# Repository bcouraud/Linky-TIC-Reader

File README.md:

# dongle_Linky

## Getting started

To make it easy for you to get started with GitLab, here's a list of recommended next steps.

Already a pro? Just edit this README.md and make it your own. Want to make it easy? [Use the template at the bottom](#editing-this-readme)!

## Add your files

- [ ] [Create](https://docs.gitlab.com/ee/user/project/repository/web_editor.html#create-a-file) or [upload](https://docs.gitlab.com/ee/user/project/repository/web_editor.html#upload-a-file) files
- [ ] [Add files using the command line](https://docs.gitlab.com/ee/gitlab-basics/add-file.html#add-a-file-using-the-command-line) or push an existing Git repository with the following command:

```
cd existing_repo
git remote add origin https://tip-imredd.unice.fr/code/energy/dongle_linky.git
git branch -M master
git push -uf origin master
```

## Integrate with your tools

- [ ] [Set up project integrations](https://tip-imredd.unice.fr/code/energy/dongle_linky/-/settings/integrations)

## Collaborate with your team

- [ ] [Invite team members and collaborators](https://docs.gitlab.com/ee/user/project/members/)
- [ ] [Create a new merge request](https://docs.gitlab.com/ee/user/project/merge_requests/creating_merge_requests.html)
- [ ] [Automatically close issues from merge requests](https://docs.gitlab.com/ee/user/project/issues/managing_issues.html#closing-issues-automatically)
- [ ] [Enable merge request approvals](https://docs.gitlab.com/ee/user/project/merge_requests/approvals/)
- [ ] [Set auto-merge](https://docs.gitlab.com/ee/user/project/merge_requests/merge_when_pipeline_succeeds.html)

## Test and Deploy

Use the built-in continuous integration in GitLab.

- [ ] [Get started with GitLab CI/CD](https://docs.gitlab.com/ee/ci/quick_start/index.html)
- [ ] [Analyze your code for known vulnerabilities with Static Application Security Testing (SAST)](https://docs.gitlab.com/ee/user/application_security/sast/)
- [ ] [Deploy to Kubernetes, Amazon EC2, or Amazon ECS using Auto Deploy](https://docs.gitlab.com/ee/topics/autodevops/requirements.html)
- [ ] [Use pull-based deployments for improved Kubernetes management](https://docs.gitlab.com/ee/user/clusters/agent/)
- [ ] [Set up protected environments](https://docs.gitlab.com/ee/ci/environments/protected_environments.html)

***

# Editing this README

When you're ready to make this README your own, just edit this file and use the handy template below (or feel free to structure it however you want - this is just a starting point!). Thanks to [makeareadme.com](https://www.makeareadme.com/) for this template.

## Suggestions for a good README

Every project is different, so consider which of these sections apply to yours. The sections used in the template are suggestions for most open source projects. Also keep in mind that while a README can be too long and detailed, too long is better than too short. If you think your README is too long, consider utilizing another form of documentation rather than cutting out information.

## Name
Choose a self-explaining name for your project.

## Description
Let people know what your project can do specifically. Provide context and add a link to any reference visitors might be unfamiliar with. A list of Features or a Background subsection can also be added here. If there are alternatives to your project, this is a good place to list differentiating factors.

## Badges
On some READMEs, you may see small images that convey metadata, such as whether or not all the tests are passing for the project. You can use Shields to add some to your README. Many services also have instructions for adding a badge.

## Visuals
Depending on what you are making, it can be a good idea to include screenshots or even a video (you'll frequently see GIFs rather than actual videos). Tools like ttygif can help, but check out Asciinema for a more sophisticated method.

## Installation
Within a particular ecosystem, there may be a common way of installing things, such as using Yarn, NuGet, or Homebrew. However, consider the possibility that whoever is reading your README is a novice and would like more guidance. Listing specific steps helps remove ambiguity and gets people to using your project as quickly as possible. If it only runs in a specific context like a particular programming language version or operating system or has dependencies that have to be installed manually, also add a Requirements subsection.

## Usage
Use examples liberally, and show the expected output if you can. It's helpful to have inline the smallest example of usage that you can demonstrate, while providing links to more sophisticated examples if they are too long to reasonably include in the README.

## Support
Tell people where they can go to for help. It can be any combination of an issue tracker, a chat room, an email address, etc.

## Roadmap
If you have ideas for releases in the future, it is a good idea to list them in the README.

## Contributing
State if you are open to contributions and what your requirements are for accepting them.

For people who want to make changes to your project, it's helpful to have some documentation on how to get started. Perhaps there is a script that they should run or some environment variables that they need to set. Make these steps explicit. These instructions could also be useful to your future self.

You can also document commands to lint the code or run tests. These steps help to ensure high code quality and reduce the likelihood that the changes inadvertently break something. Having instructions for running tests is especially helpful if it requires external setup, such as starting a Selenium server for testing in a browser.

## Authors and acknowledgment
Show your appreciation to those who have contributed to the project.

## License
For open source projects, say how it is licensed.

## Project status
If you have run out of energy or time for your project, put a note at the top of the README saying that development has slowed down or stopped completely. Someone may choose to fork your project or volunteer to step in as a maintainer or owner, allowing your project to keep going. You can also make an explicit request for maintainers.

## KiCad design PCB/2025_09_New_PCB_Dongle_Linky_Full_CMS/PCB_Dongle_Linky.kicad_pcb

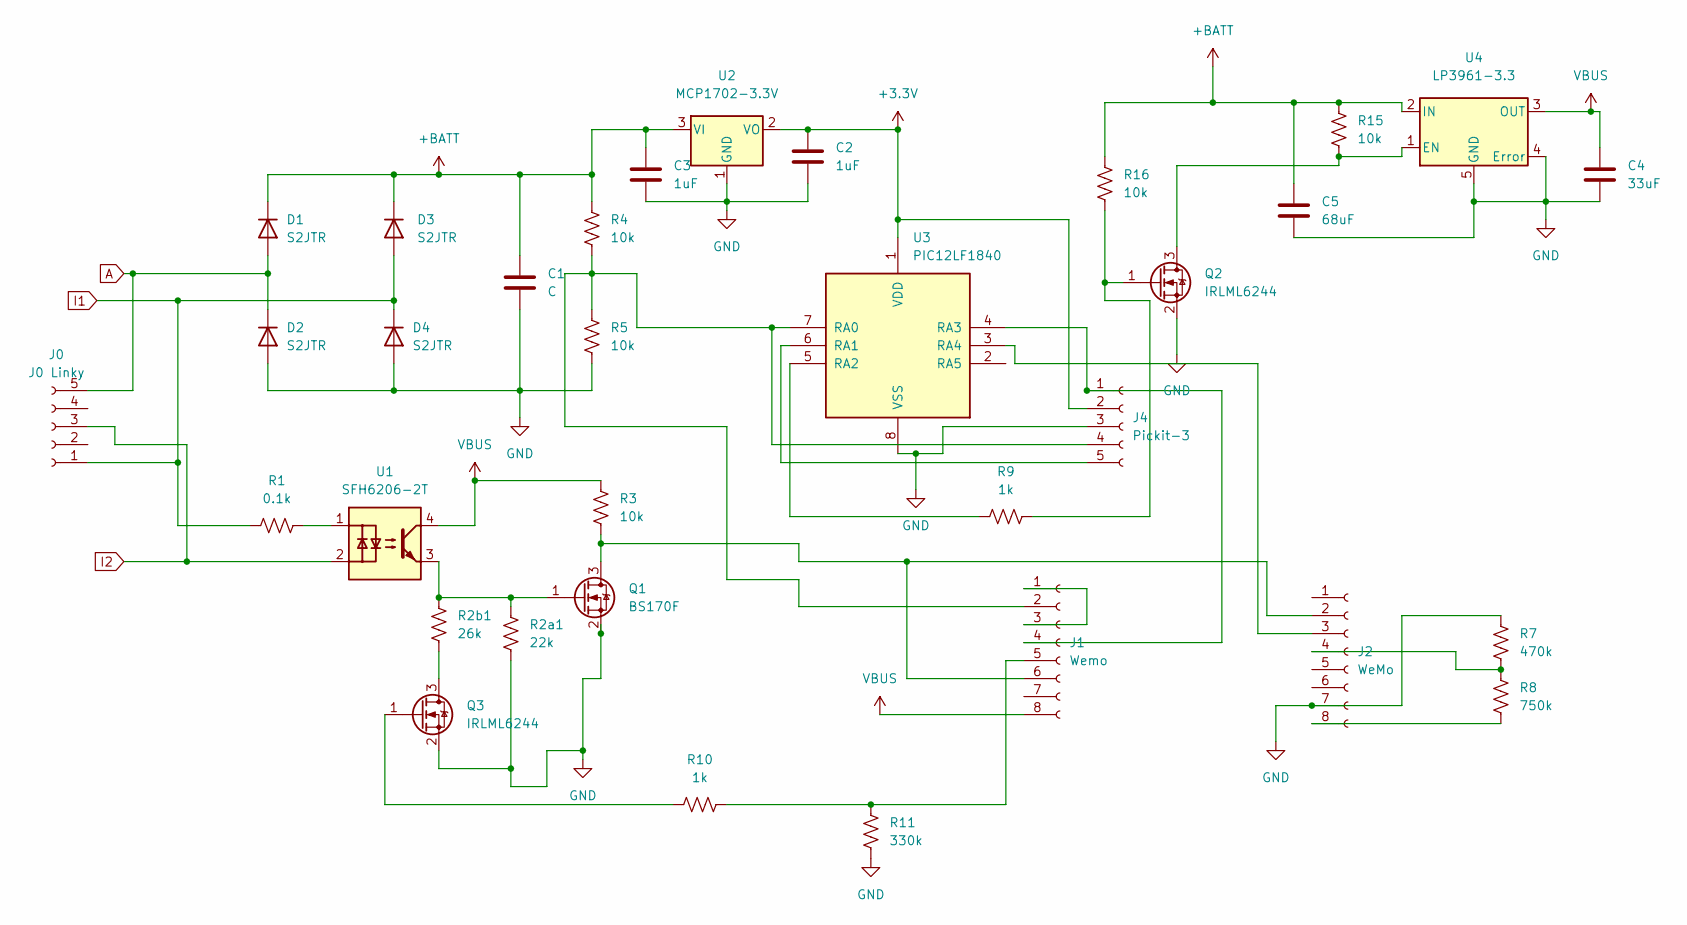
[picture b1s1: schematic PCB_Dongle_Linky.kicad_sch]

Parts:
C1: C; C_Rect_L19.0mm_W11.0mm_P15.00mm_MKS4
C2, C3: 1uF; C_0805_2012Metric
C4: 33uF; C_0805_2012Metric
C5: 68uF; C_0805_2012Metric
D1, D2, D3, D4: S2JTR; D_SMB
J0: J0 Linky; PinHeader_1x05_P2.54mm_Vertical
J1: Wemo; PinHeader_1x08_P2.54mm_Vertical
J2: WeMo; PinHeader_1x08_P2.54mm_Vertical
J4: Pickit-3; PinHeader_1x05_P2.54mm_Vertical
Q1: BS170F; SOT-23
Q2, Q3: IRLML6244; SOT-23
R1: 0.1k; R_0805_2012Metric
R2a1: 22k; R_0805_2012Metric
R2b1: 26k; R_0805_2012Metric
R3, R4, R5, R15, R16: 10k; R_0805_2012Metric
R7: 470k; R_0805_2012Metric
R8: 750k; R_0805_2012Metric
R9, R10: 1k; R_0805_2012Metric
R11: 330k; R_0805_2012Metric
U1: SFH6206-2T; SMDIP-4_W9.53mm_Clearance8mm
U2: MCP1702-3.3V; SOT-23
U3: PIC12LF1840; SOIC-8_3.9x4.9mm_P1.27mm
U4: LP3961-3.3; SOT-223-5

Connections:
+3.3V: C2.1, J4.2, U2.2 (VO), U3.1 (VDD)
+BATT: C1.1, C3.1, C5.1, D1.1 (K), D3.1 (K), R4.2, R15.1, R16.1, U2.3 (VI), U4.2 (IN)
A: D1.2 (A), D2.1 (K), J0.5
GND: C1.2, C2.2, C3.2, C4.2, C5.2, D2.2 (A), D4.2 (A), J2.7, J4.3, Q1.2 (S), Q2.2 (S), Q3.2 (S), R2a1.1, R5.1, R7.2, R11.2, U2.1 (GND), U3.8 (VSS), U4.4 (Error), U4.5 (GND)
I1: D3.2 (A), D4.1 (K), J0.1, R1.1
I2: J0.3, U1.2
unnamed: J1.1, J1.3
unnamed: J1.2, J4.4, R4.1, R5.2, U3.7 (RA0)
unnamed: J1.4, J4.1, U3.4 (RA3)
unnamed: J1.5, R10.1, R11.1
unnamed: J1.6, J2.2, Q1.3 (D), R3.1
unnamed: J2.3, U3.3 (RA4)
unnamed: J2.4, R7.1, R8.2
unnamed: J2.8, R8.1
unnamed: J4.5, U3.6 (RA1)
unnamed: Q1.1 (G), R2a1.2, R2b1.2, U1.3
unnamed: Q2.1 (G), R9.1, R16.2
unnamed: Q2.3 (D), R15.2, U4.1 (EN)
unnamed: Q3.1 (G), R10.2
unnamed: Q3.3 (D), R2b1.1
unnamed: R1.2, U1.1
unnamed: R9.2, U3.5 (RA2)
VBUS: C4.1, J1.8, R3.2, U1.4, U4.3 (OUT)

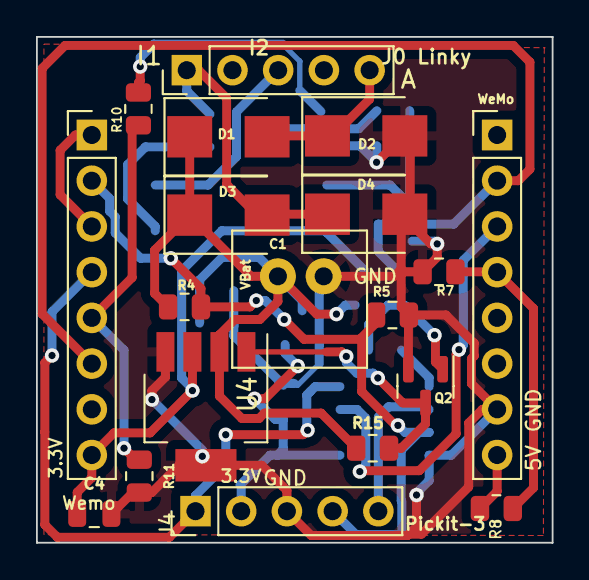
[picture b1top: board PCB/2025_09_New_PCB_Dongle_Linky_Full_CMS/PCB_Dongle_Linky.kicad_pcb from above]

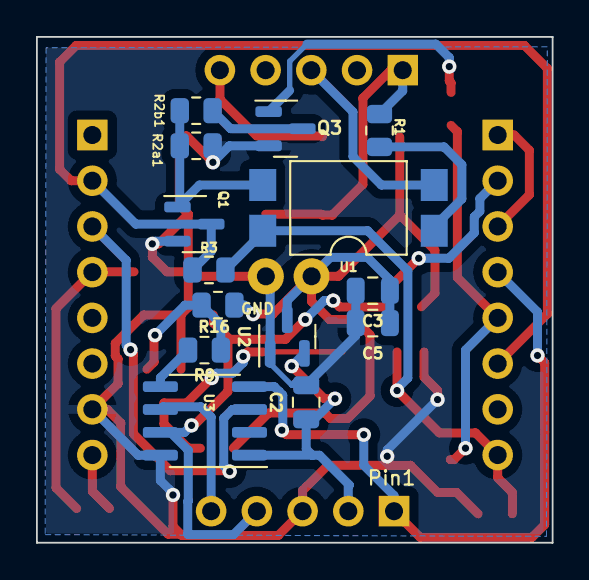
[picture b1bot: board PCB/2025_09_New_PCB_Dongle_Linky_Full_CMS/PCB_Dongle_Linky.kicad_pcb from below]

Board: 2 copper layers, 28.6 x 28.1 mm, 33 parts (14 on the bottom side), 23 nets.

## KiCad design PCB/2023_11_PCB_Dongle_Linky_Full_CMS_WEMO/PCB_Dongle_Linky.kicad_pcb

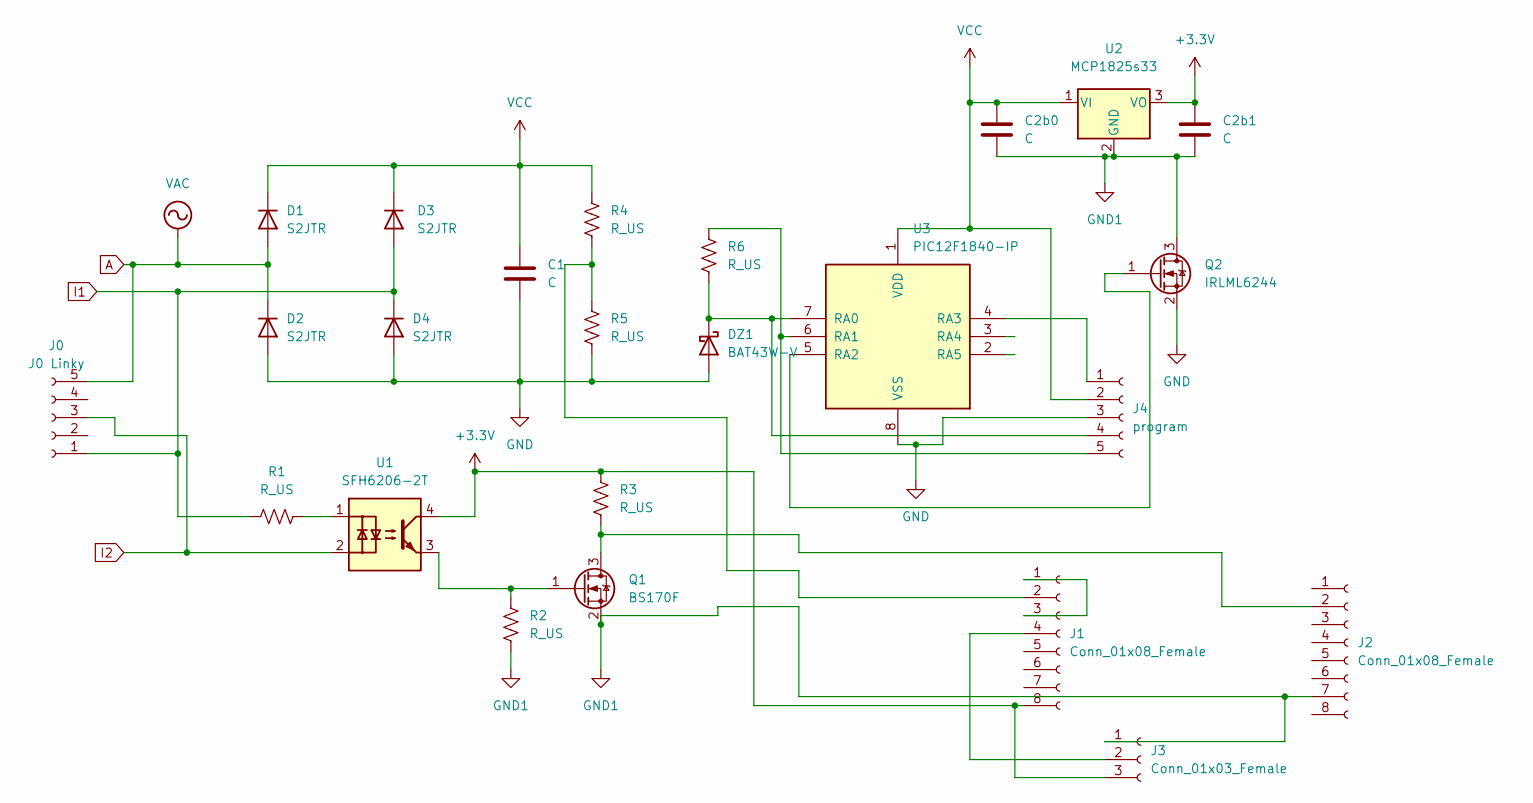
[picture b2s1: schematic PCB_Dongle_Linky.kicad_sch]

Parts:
C1: C; C_Rect_L19.0mm_W11.0mm_P15.00mm_MKS4
C2b0, C2b1: C; C_0805_2012Metric
D1, D2, D3, D4: S2JTR; D_SMB
DZ1: BAT43W-V; D_SOD-123
J0: J0 Linky; PinHeader_1x05_P2.54mm_Vertical
J1, J2: Conn_01x08_Female; PinHeader_1x08_P2.54mm_Vertical
J3: Conn_01x03_Female; PinHeader_1x03_P2.54mm_Vertical
J4: program; PinHeader_1x05_P2.54mm_Vertical
Q1: BS170F; SOT-23
Q2: IRLML6244; SOT-23
R1, R2, R3, R4, R5, R6: R_US; R_0805_2012Metric
U1: SFH6206-2T; SMDIP-4_W9.53mm_Clearance8mm
U2: MCP1825s33; SOT-223-3_TabPin2
U3: PIC12F1840-IP; SOIC-8_3.9x4.9mm_P1.27mm

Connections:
+3.3V: C2b1.1, J1.8, J3.3, R3.2, U1.4, U2.3 (VO)
A: D1.2 (A), D2.1 (K), J0.5
GND: C1.2, D2.2 (A), D4.2 (A), DZ1.2 (A), J4.3, Q2.2 (S), R5.1, U3.8 (VSS)
GND1: C2b0.2, C2b1.2, J2.7, J3.1, Q1.2 (S), Q2.3 (D), R2.1, U2.2 (GND)
I1: D3.2 (A), D4.1 (K), J0.1, R1.1
I2: J0.3, U1.2
unnamed: DZ1.1 (K), J4.4, R6.1, U3.7 (RA0)
unnamed: J1.1, J1.3
unnamed: J1.2, R4.1, R5.2
unnamed: J1.4, J3.2
unnamed: J2.2, Q1.3 (D), R3.1
unnamed: J4.1, U3.4 (RA3)
unnamed: J4.5, R6.2, U3.6 (RA1)
unnamed: Q1.1 (G), R2.2, U1.3
unnamed: Q2.1 (G), U3.5 (RA2)
unnamed: R1.2, U1.1
VCC: C1.1, C2b0.1, D1.1 (K), D3.1 (K), J4.2, R4.2, U2.1 (VI), U3.1 (VDD)

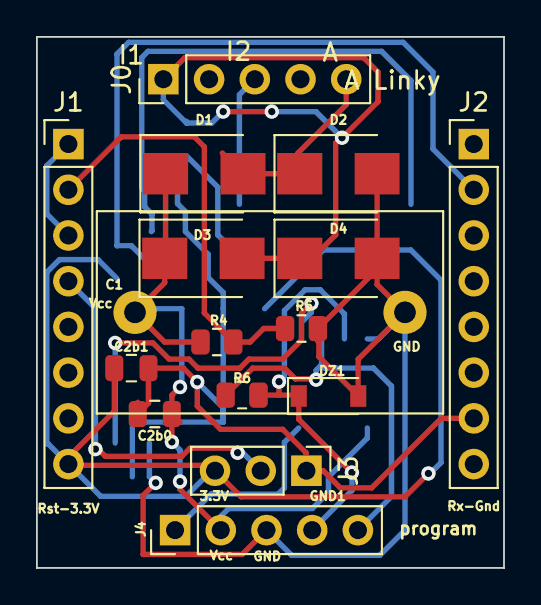
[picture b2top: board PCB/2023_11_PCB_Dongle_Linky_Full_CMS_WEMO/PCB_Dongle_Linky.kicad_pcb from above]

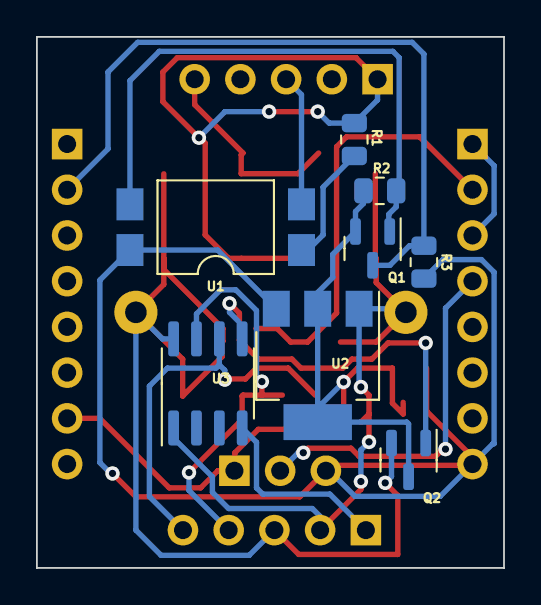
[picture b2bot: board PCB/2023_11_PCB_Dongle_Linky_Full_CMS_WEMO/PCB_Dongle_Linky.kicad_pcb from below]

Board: 2 copper layers, 26.0 x 29.5 mm, 24 parts (8 on the bottom side), 17 nets.

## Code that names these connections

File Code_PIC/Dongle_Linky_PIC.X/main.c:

// For Vref (supply) =5V:
//ADC = 24 --> 0.47V 
// ADC = 48 --> 0.95 
// ADC = 100 --> 1.96V
// ADC = 150 --> 2.98V
// ADC = 200 --> 3.96V
// ADC = 250 --> 4.98V







// CONFIG1
#pragma config FOSC = INTOSC    
#pragma config WDTE = ON       
#pragma config PWRTE = OFF      
#pragma config MCLRE = ON    // RA3 is digital input/output (not MCLR)
#pragma config CP = OFF         
#pragma config CPD = OFF        
#pragma config BOREN = ON       
#pragma config CLKOUTEN = OFF   
#pragma config IESO = ON        
#pragma config FCMEN = ON       

// CONFIG2
#pragma config WRT = OFF        
#pragma config PLLEN = ON       
#pragma config STVREN = ON      
#pragma config BORV = LO        
#pragma config LVP = OFF        

#define _XTAL_FREQ 1000000

#include <xc.h>
#include <math.h>
//#include <stdbool.h>

// ----------- Global Variables -----------
unsigned int counter_ADC = 0;
unsigned int counter_RisingVoltage = 0;
unsigned int counter_Reset = 0;
unsigned int limit_ADC = 1; //1;          // ~1 cycles of 1s
unsigned int limit_RisingVoltage = 4; //1;          // ~4 cycles of 1s
unsigned int limit_Reset = 35;          // ~60 cycles of 1s ~ 1 minute  (8 cycles = 14s)
unsigned char threshold3 = 146 ; //590; //147 * 1023 / 255 ; 147;   // 6.1V Voltage must rise to this
unsigned char threshold4 = 151 ; //605; //151 * 1023 / 255 ? 605     ; 151;   // 5.7V Voltage low threshold (from zener)
unsigned char adc_char = 0;
unsigned char last_adc = 0;
unsigned char voltage_rised = 0;
unsigned char currentState = 0;

// ----------- ADC Function (10-bit accuracy, returns 8-bit) -----------
unsigned int ADC_Lecture(void) {
    ADCON0bits.ADON = 1;          // Turn on ADC
    __delay_ms(2);                // Acquisition time
    ADCON0bits.GO = 1;            // Start conversion
    while (ADCON0bits.GO_nDONE); // Wait until done

    return (ADRESH);//return ((ADRESH << 8) | ADRESL); // Combine high + low byte
}

// ----------- Optional WDT delay function -----------
void delayWithWDT(unsigned int cycles) {
    for (unsigned int i = 0; i < cycles; i++) {
        CLRWDT();
        __delay_ms(10);  // Keep < WDT timeout (~1s)
    }
}

// ----------- Main -----------
void main(void) {
    // --- WDT + Oscillator setup ---
    CLRWDT();
    OPTION_REGbits.PSA = 1;      
    OPTION_REGbits.PS = 0b111;   // 1:256
    INTCON = 0;
    PIE1 = 0;
    PIR1 = 0;
    OSCCON = 0b01011010;         // Internal OSC, 1MHz
    OSCCONbits.SCS1 = 1;

    // --- IO setup ---
    TRISA = 0b00000001;          // RA0 = input (ADC), others output
    LATA = 0x00;
    ANSELAbits.ANSA0 = 1;        // RA0 analog
    ADCON1bits.ADCS = 0b000;
    ADCON1bits.ADPREF = 0b00;    
    ADCON1bits.ADFM = 0; // left-justified (8-bits)1;  // Right justified (10-bit)
    ADCON0bits.CHS = 0b0000;     // RA0
    APFCONbits.P1BSEL = 0;
    TRISAbits.TRISA3 = 0;    // Make RA3 an output

    // INIT UART
            APFCONbits.RXDTSEL = 1; //Select RX on RA5 (instead of RA0)
            APFCONbits.TXCKSEL = 1; //Select TX on RA4 (instead of RA1)
            APFCONbits.P1BSEL = 0 ;
            TRISAbits.TRISA4 = 0;   // RA4 = TX= output
            TRISAbits.TRISA5 = 1;   // RA5 = RX = INPUT
            //Configuration Data Rate
            BAUDCONbits.BRG16 = 1;//0;
            SPBRG = 25;   // = Fosc/(16*DataRate)-1;  Fosc = 1MHz et DataRate = 9600
            //SPBRGH=25>>8;
            //SPBRGL = 25&0xFF;
            TXSTA = 0b00110110; // Asynchron TX config, sur 8bits,
            TXSTAbits.BRGH = 1;
            TXSTAbits.SYNC = 0;
            RCSTA = 0b10010000; // Asynchron RX config, sur 8 bits
    
    
    
    
    
    
    
    
    
    // --- Initial Power ON ---
    LATAbits.LATA1 = 1;         // Start lecture by putting power on resistance and diode
    last_adc = ADC_Lecture();
    LATAbits.LATA1 = 0;         // 

    delayWithWDT(1);          // Initial wait if needed

    while (1) {
        counter_ADC++;
        counter_Reset++;
        counter_RisingVoltage++;
            //delayWithWDT(2);          // Initial wait if needed

        LATAbits.LATA1 = 0;   // Ensure pin powers off on resistance and diode
        SLEEP();                // Sleep ~1s (WDT)
        NOP();

        if (counter_ADC >= limit_ADC) {
            counter_ADC = 0;
          //  LATAbits.LATA2 ^= 1;

                LATAbits.LATA1 =1;  // Start lecture by putting power on resistance and diode
                adc_char = ADC_Lecture();
                LATAbits.LATA1 =0;
                
                // we send the result through UART 
                   // TXREG = 00;
                   // while(!TXSTAbits.TRMT);
                    //TXREG = adc_char;
                    //while(!TXSTAbits.TRMT); // we send the result through UART 
                
                
                
                
                
               if (adc_char<threshold3){ // if we reached 6V   (1.4V when supplied at 5V in a test (without zener diode))
                   currentState = 1;
                   LATAbits.LATA2=1;
               }else if(adc_char>threshold4){// if we go below 5.8V
                    LATAbits.LATA2=0;
               }                
                
            }
        if (counter_RisingVoltage >= limit_RisingVoltage) {
            counter_RisingVoltage = 0;
                if (adc_char<last_adc-2){
                    voltage_rised = 1;
                   // TXREG = 255;
                   // while(!TXSTAbits.TRMT); // we send the result through UART 
                }
            
            last_adc = adc_char;
            
        }
        
        
        if (counter_Reset >= limit_Reset) {
            counter_Reset = 0;   
                    //            TXREG = 19;
                    //while(!TXSTAbits.TRMT); // we send the result through UART 


            if (voltage_rised==0){ // if there was no increase in voltage during the whole minute
               LATAbits.LATA2 = 0; // Voltage did not recover, turn off to reset
               delayWithWDT(10);          // Initial wait if needed
                   // TXREG = 255;
                    //while(!TXSTAbits.TRMT); // we send the result through UART 
 

            }
            voltage_rised = 0;
        }

    }
}

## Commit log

2025-07-29 update_July_2025 updated PCB PIC code ESP
2025-07-29 update_July_2025 updated PIC
2025-08-16 Modified PIC and ESP codes
2025-10-28 New version of Watty 2025
2025-10-28 Added Installation manual
